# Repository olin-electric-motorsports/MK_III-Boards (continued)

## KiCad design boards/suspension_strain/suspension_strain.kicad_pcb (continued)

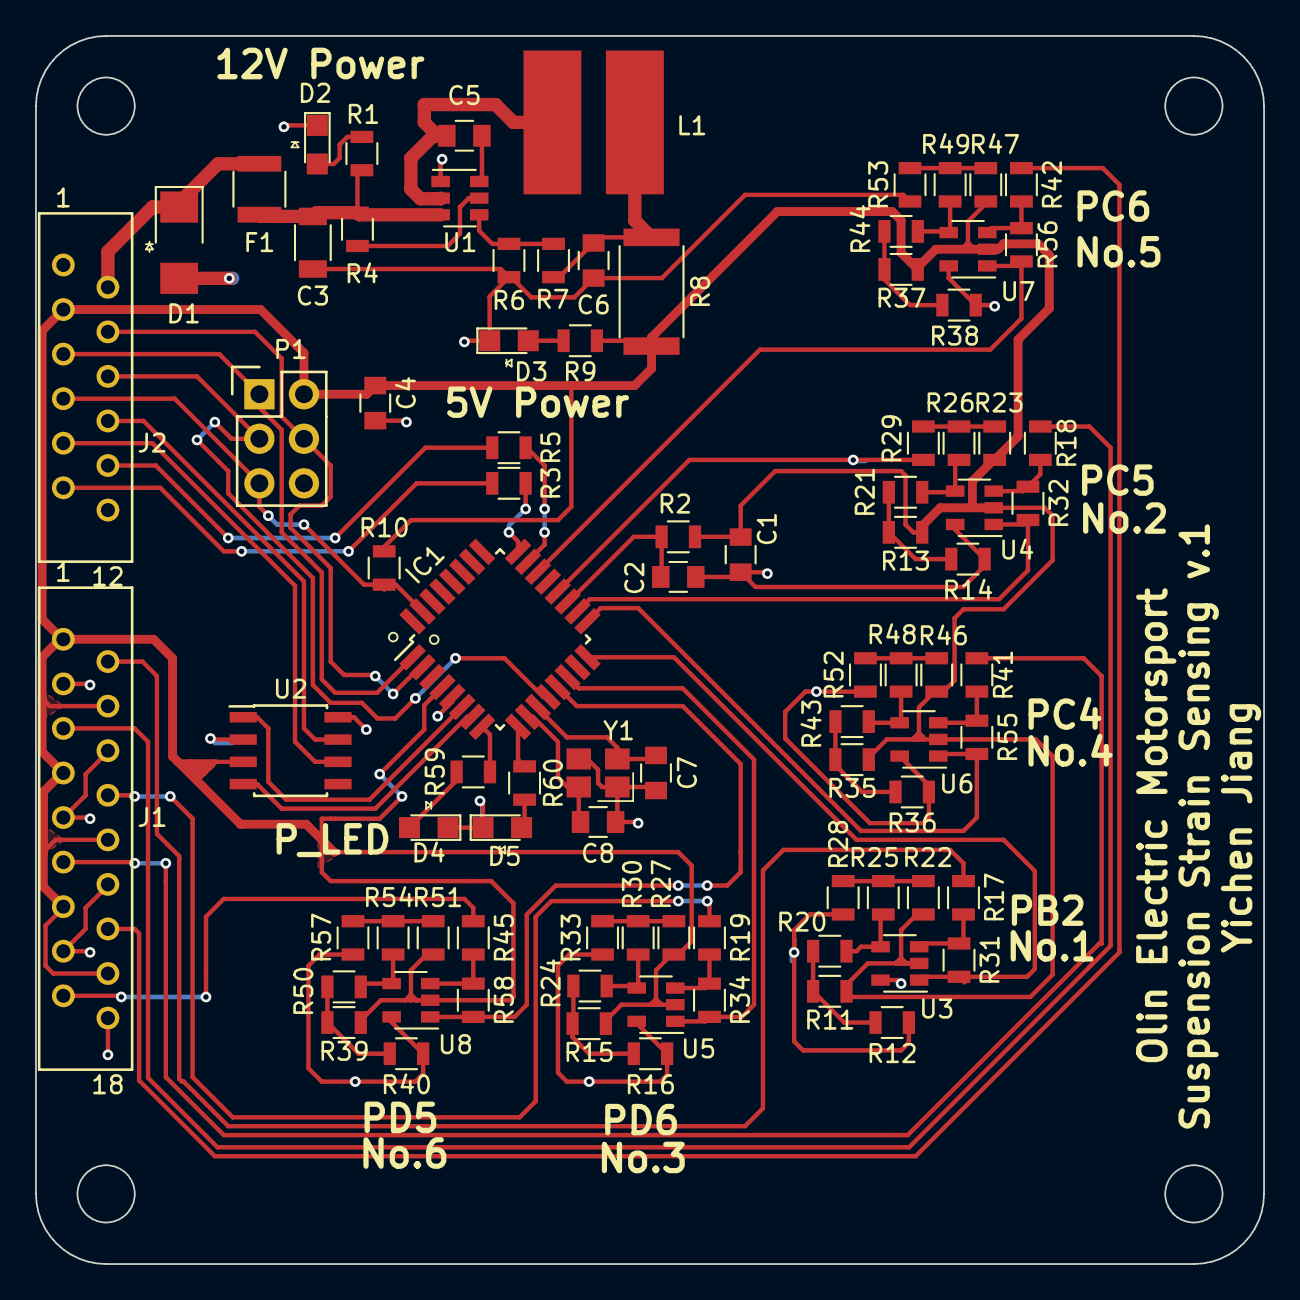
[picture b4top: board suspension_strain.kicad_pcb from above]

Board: 2 copper layers, 70.0 x 70.0 mm, 88 parts (0 on the bottom side), 66 nets.

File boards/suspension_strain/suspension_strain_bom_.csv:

Component,Description,Part,References,Value,Footprint,Quantity Per PCB,Datasheet,Package,MPN,MFN,PurchasingLink
1,Cap 50V 0.1uF 10% 0805,C_0.1uF,C1 C4 C5,C_0.1uF,C_0805_OEM,3,http://datasheets.avx.com/X7RDielectric.pdf,Value,478-3352-1-ND,Digi-Key,https://www.digikey.com/products/en?keywords=478-3352-1-ND
2,Cap 50V 100pF 5% 0805,C_100pF,C2,C_100pF,C_0805_OEM,1,https://content.kemet.com/datasheets/KEM_C1003_C0G_SMD.pdf,Value,399-1122-1-ND,Digi-Key,https://www.digikey.com/product-detail/en/kemet/C0805C101J5G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
3,Unpolarized capacitor,C_22uF,C3,C_22uF,C_1206_OEM,1,http://www.samsungsem.com/kr/support/product-search/mlcc/__i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,Value,1276-2725-1-ND,Digi-Key,https://www.digikey.com/products/en?keywords=1276-2725-1-ND
4,Cap 50V 30pF 5% 0805,C_30pF,C7 C8,C_30pF,C_0805_OEM,2,https://media.digikey.com/pdf/Data%20Sheets/Samsung%20PDFs/C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,Value,1276-1130-1-ND,Digi-Key,https://www.digikey.com/product-detail/en/samsung-electro-me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
5,CAP CER 47UF 6.3V X5R 0805,C_47uF,C6,C_47uF,C_0805_OEM,1,http://www.yuden.co.jp/productdata/catalog/en/mlcc_all_e.pdf,Value,587-4280-1-ND,Digi-Key,https://www.digikey.com/product-detail/en/taiyo-yuden/JMK212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
6,DIODE ZENER 18V 5W DO214AA,D_Zener_18V,D1,D_Zener_18V,DO-214AA,1,http://www.mccsemi.com/up_pdf/SMBJ5338B-SMBJ5388B(SMB).pdf,DO-214AA (SMB),SMBJ5355B-TPMSCT-ND,Digi-Key,https://www.digikey.com/products/en?keywords=SMBJ5355B-TPMSCT-ND
7,LED_0805,LED_0805,D2 D3 D4 D5,LED_0805,LED_0805_OEM,4,http://www.osram-os.com/Graphics/XPic9/00078860_0.pdf,Value,475-1410-1-ND,Digi-Key,https://www.digikey.com/products/en?keywords=475-1410-1-ND
8,PTC Fuse 16V 500mA,F_500mA_16V,F1,F_500mA_16V,Fuse_1210,1,https://belfuse.com/resources/CircuitProtection/datasheets/0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,Value,507-1786-1-ND,Digi-Key,https://www.digikey.com/product-detail/en/bel-fuse-inc/0ZCH0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
9,"TQFP32, 16k Flash, 1k SRAM, 512B EEPROM, CAN",ATMEGA16M1,IC1,ATMEGA16M1,TQFP-32_7x7mm_Pitch0.8mm,1,http://www.atmel.com/Images/Atmel-8209-8-bit%20AVR%20ATmega1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,Value,ATMEGA16M1-AU-ND,Digi-Key,https://www.digikey.com/product-detail/en/atmel/ATMEGA16M1-A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
10,connector micromatch female RA 12,micromatch_female_RA_12,J2,micromatch_female_RA_12,micromatch_female_ra_12,1,,Value,A99486CT-ND,Digi-Key,https://www.digikey.com/product-detail/en/te-connectivity-am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
11,connector micromatch female RA 18,micromatch_female_RA_18,J1,micromatch_female_RA_18,micromatch_female_ra_18,1,,Value,A99489CT-ND,Digi-Key,https://www.digikey.com/product-detail/en/te-connectivity-am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
12,Inductor 4.7uH 4.4A,L_4.7uH,L1,L_4.7uH,4.7uH_Inductor_OEM,1,https://product.tdk.com/info/en/documents/wdcatalog/withdraw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,Value,445-6583-1-ND,Digi-Key,https://www.digikey.com/product-detail/en/tdk-corporation/VL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
13,"Connector, double row, 02x03",CONN_02X03,P1,CONN_02X03,Pin_Header_Straight_2x03,1,http://portal.fciconnect.com/Comergent//fci/drawing/67996.pdf,Value,609-3234-ND,Digi-Key,https://www.digikey.com/product-detail/en/amphenol-fci/67997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
14,Res 0 2512 3W Jumper,R_0_Jumper,R8,R_0_Jumper,R_2512_OEM,1,http://www.te.com/commerce/DocumentDelivery/DDEController?Ac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,Value,A121322CT-ND,Digi-Key,https://www.digikey.com/products/en?keywords=A121322CT-ND
15,Res 100 1%,R_100,R2 R22 R23 R27 R28 R29 R33 R46 R47 R51 R52 R53 R57,R_100,R_0805_OEM,13,https://www.seielect.com/Catalog/SEI-rncp.pdf,Value,RNCP0805FTD100RCT-ND,Digi-Key,https://www.digikey.com/products/en?keywords=RNCP0805FTD100RCT-ND
16,Res 100k 1%,R_100k,R25 R26 R30 R31 R32 R34 R48 R49 R54 R55 R56 R58,R_100k,R_0805_OEM,12,http://www.yageo.com.tw/exep/pages/download/literatures/PYu-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,Value,311-100KCRCT-ND,Digi-Key,https://www.digikey.com/products/en?keywords=311-100KCRCT-ND
17,Res 10k 1%,R_10k,R4 R6 R10,R_10k,R_0805_OEM,3,http://www.bourns.com/data/global/pdfs/CRS.pdf,Value,CRS0805-FX-1002ELFCT-ND,Digi-Key,https://www.digikey.com/products/en?keywords=CRS0805-FX-1002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
18,Res 1k 1%,R_1k,R1 R17 R18 R19 R20 R21 R24 R41 R42 R43 R44 R45 R50,R_1k,R_0805_OEM,13,https://www.seielect.com/Catalog/SEI-rncp.pdf,Value,RNCP0805FTD1K00CT-ND,Digi-Key,https://www.digikey.com/products/en?keywords=RNCP0805FTD1K00CT-ND
19,Res 200 5%,R_200,R3 R5 R9 R59 R60,R_200,R_0805_OEM,5,https://www.seielect.com/Catalog/SEI-RMCF_RMCP.pdf,Value,RMCF0805JT200RCT-ND,Digi-Key,https://www.digikey.com/products/en?keywords=RMCF0805JT200RCT-ND
20,Resistor 500Ohm 0.1%,R_500,R11 R12 R13 R14 R15 R16 R35 R36 R37 R38 R39 R40,R_500,R_0805_OEM,12,http://www.vishay.com/docs/60057/pnm.pdf,Value,541-1905-2-ND,Digi Key,https://www.digikey.com/product-detail/en/vishay-dale/PNM040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
21,Res 55.1k 1%,R_55.1k,R7,R_55.1k,R_0805_OEM,1,http://www.yageo.com.tw/exep/pages/download/literatures/PYu-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,Value,311-51.1KCRCT-ND,Digi-Key,https://www.digikey.com/products/en?keywords=311-51.1KCRCT-ND
22,"High-Speed CAN Transceiver, 1Mbps, 5V supply, SPLIT pin, -40C to +125C, SOIC8 package",CAN_Transceiver,U2,CAN_Transceiver,SOIC-8_3.9x4.9mm_Pitch1.27mm_OEM,1,http://www.microchip.com/mymicrochip/filehandler.aspx?ddocna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,Value,MCP2561-E/SN-ND,Digi-Key,https://www.digikey.com/products/en?keywords=mcp2561-e%2Fsn
23,IC OPAMP GP 1MHZ RRO SOT23-5  1.8-6V,MCP6001RT,U3 U4 U5 U6 U7 U8,MCP6001RT,SOT-23-5_OEM,6,http://ww1.microchip.com/downloads/en/DeviceDoc/21733j.pdf,,MCP6001RT-I/OTCT-ND,Digi-Key,https://www.digikey.com/product-detail/en/microchip-technolo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
24,4.5V - 17V Input 1A Synchronous Buck Converter,TPS561201,U1,TPS561201,SOT-23-6_OEM,1,http://www.ti.com/lit/ds/symlink/tps561201.pdf,Value,TPS561201,Digi-Key,https://www.digikey.com/products/en?keywords=296-46928-1-ND
25,"Two pin crystal, two ground/package pins (pin2 and 3) small symbol",Crystal_SMD,Y1,Crystal_SMD,Crystal_SMD_FA238,1,https://support.epson.biz/td/api/doc_check.php?dl=brief_FA-2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,Value,SER3686CT-ND,Digi-Key,https://www.digikey.com/products/en?keywords=SER3686CT-ND





Component Groups:,25
Component Count:,88
Fitted Components:,88
Number of PCBs:,1
Total components:,88
Schematic Version:,
Schematic Date:,
BoM Date:,Tue 05 Dec 2017 08:39:58 PM EST
Schematic Source:,/home/yichen/Documents/Projects/Formula/MK_III-Boards/boards/suspension_strain/suspension_strain.sch
KiCad Version:,Eeschema 4.0.7-e2-6376~58~ubuntu16.04.1

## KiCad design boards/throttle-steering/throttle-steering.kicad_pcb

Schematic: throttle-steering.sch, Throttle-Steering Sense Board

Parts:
C1, C2, C5: C_0.1uF; C_0805_OEM; MPN 478-3352-1-ND
C3: C_100pF; C_0805_OEM; MPN 399-1122-1-ND
C4: C_22uF; C_1206_OEM; MPN 1276-2725-1-ND
C6, C8: C_30pF; C_0805_OEM; MPN 1276-1130-1-ND
C7: C_47uF; C_0805_OEM; MPN 587-4280-1-ND
D1, D2, D3, D4, D5, D6: LED_0805; LED_0805_OEM; MPN 475-1410-1-ND
D7: D_Zener_18V; DO-214AA; MPN SMBJ5355B-TPMSCT-ND
D8, D9: LED_0805; D_0805_OEM; MPN 475-1410-1-ND
F1: F_500mA_16V; Fuse_1210; MPN 507-1786-1-ND
IC1: ATMEGA16M1; TQFP-32_7x7mm_Pitch0.8mm; MPN ATMEGA16M1-AU-ND
J1: micromatch_female_RA_20; micromatch_female_ra_20; MPN A99490CT-ND
J2: micromatch_female_RA_4; micromatch_female_ra_4; MPN A99482CT-ND
L1: L_4.7uH; 4.7uH_Inductor_OEM; MPN 445-6583-1-ND
P1: CONN_02X03; Pin_Header_Straight_2x03; MPN 609-3234-ND
Q1, Q2, Q3: SSM3K333R; SOT-23F; MPN SSM3K333RLFCT-ND
R1, R2, R3, R24, R25, R28: R_200; R_0805_OEM; MPN RMCF0805JT200RCT-ND
R4, R13: R_1M; R_0805_OEM; MPN RMCF0805JT1M00CT-ND
R5, R7, R10, R15, R16, R20: R_1k; R_0805_OEM; MPN RNCP0805FTD1K00CT-ND
R6, R11, R17: R_100k; R_0805_OEM; MPN 311-100KCRCT-ND
R8, R14: R_2.2k; R_0805_OEM; MPN RMCF0805FT2K20CT-ND
R9, R12, R18, R21, R22, R27: R_10k; R_0805_OEM; MPN CRS0805-FX-1002ELFCT-ND
R19: R_100; R_0805_OEM; MPN RNCP0805FTD100RCT-ND
R23: R_55.1k; R_0805_OEM; MPN 311-51.1KCRCT-ND
R26: R_0_Jumper; R_2512_OEM; MPN A121322CT-ND
U1, U3: MCP6001RT; SOT-23-5_OEM; MPN MCP6001RT-I/OTCT-ND
U2: CAN_Transceiver; SOIC-8_3.9x4.9mm_Pitch1.27mm_OEM; MPN MCP2561-E/SN-ND
U4: TPS561201; SOT-23-6_OEM; MPN TPS561201
Y1: Crystal_SMD; Crystal_SMD_FA238; MPN SER3686CT-ND

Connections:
+12V: D7.1 (K), F1.1, J2.2
/CANH: J2.8, U2.7 (CANH)
/CANL: J2.9, U2.6 (CANL)
/LED1: J2.10, R24.1
/LED2: J2.11, R25.1
/MISO: IC1.1 ((PCINT18/PSCIN2/OC1A/MISO_A)PD2), J2.5, P1.1
/MOSI: IC1.2 ((PCINT19/TXD/TXLIN/OC0A/~SS~/MOSI_A)PD3), J2.4, P1.4
/PLED1: D1.2 (A), IC1.22 ((PCINT14/ADC10/ACMP1)PC6)
/PLED2: D2.2 (A), IC1.23 ((PCINT3/AMP0-)PB3)
/PLED3: D3.2 (A), IC1.24 ((PCINT4/AMP0+)PB4)
/RESET: IC1.31 ((PCINT24/OCD/~RESET~)PE0), J2.7, P1.5, R27.2
/RTD: J1.4; also elsewhere on the board
/RXCAN: IC1.7 ((PCINT11/T1/ICP1B/RXCAN)PC3), U2.4 (RXD)
/SCK: IC1.12 ((PCINT20/ADC1/RXD/RXLIN/ICP1A/SCK_A)PD4), J2.6, P1.3
/SS_BOTS: J1.1, Q3.1 (G), R16.1, R17.1
/SS_BOTS_Out: IC1.28 ((PCINT7/ADC4/SCK/PSCOUT0B)PB7), Q3.3 (D), R18.2
/SS_Cockpit_EStop: J1.2, Q2.1 (G), R10.1, R11.1
/SS_EStop_Out: IC1.27 ((PCINT6/ADC7/PSCOUT1B)PB6), Q2.3 (D), R12.2
/SS_IS_Out: IC1.26 ((PCINT5/ADC6/INT2/ACMPN1/AMP2-)PB5), Q1.3 (D), R9.2
/SS_Inertia_Switch: J1.3, Q1.1 (G), R5.1, R6.1
/Steering_Sense: IC1.13 ((PCINT21/ADC2/ACMP2)PD5), J2.19
/TXCAN: IC1.6 ((PCINT10/T0/TXCAN)PC2), U2.1 (TXD)
/Throttle1OutL: IC1.17 ((PCINT12/ADC8/ACMPN3/AMP1-)PC4), R14.1, U3.1
/Throttle2OutR: IC1.18 ((PCINT13/ADC9/ACMP3/AMP1+)PC5), R7.1, U1.1
/Throttle_Left_Sense: J2.13, R13.2, U3.3 (+)
/Throttle_Right_Sense: J2.16, R4.2, U1.3 (+)
GND: C1.2, C2.2, C3.2, C4.2, C6.2, C7.2, C8.2, D4.1 (K), D5.1 (K), D6.1 (K), D7.2 (A), D8.1 (K), D9.1 (K), IC1.5 (GND), IC1.20 (AGND), J2.1, J2.14, J2.17, J2.20, P1.6, Q1.2 (S), Q2.2 (S), Q3.2 (S), R1.2, R2.2, R3.2, R6.2, R8.2, R11.2, R15.2, R17.2, R22.2, U1.5 (V-), U2.2 (VSS), U2.8 (STBY), U3.5 (V-), U4.1 (GND), Y1.2, Y1.4; also elsewhere on the board
unnamed: C3.1, IC1.19 (AVCC), R19.2
unnamed: C4.1, F1.2, R20.1, R21.1, U4.3 (VIN)
unnamed: C5.1, U4.6 (VBST)
unnamed: C5.2, L1.1, U4.2 (SW)
unnamed: C6.1, IC1.11 ((PCINT26/ADC0/XTAL2)PE2), Y1.1
unnamed: C8.1, IC1.10 ((PCINT25/OC0B/XTAL1)PE1), Y1.3
unnamed 33: C7.1, L1.2, R23.2, R26.2; also elsewhere on the board
unnamed: D1.1 (K), R1.1
unnamed: D2.1 (K), R2.1
unnamed: D3.1 (K), R3.1
unnamed: D4.2 (A), R5.2
unnamed: D5.2 (A), R10.2
unnamed: D6.2 (A), R16.2
unnamed: D8.2 (A), R20.2
unnamed: D9.2 (A), R28.2
unnamed: IC1.8 ((PCINT0/MISO/PSCOUT2A)PB0), R24.2
unnamed: IC1.9 ((PCINT1/MOSI/PSCOUT2B)PB1), R25.2
unnamed: R7.2, R8.1, U1.4 (-)
unnamed: R14.2, R15.1, U3.4 (-)
unnamed: R21.2, U4.5 (EN)
unnamed: R22.1, R23.1, U4.4 (VFB)
RTD_LD: IC1.25 ((PCINT15/D2A/AMP2+)PC7); also elsewhere on the board
VCC: C1.1, C2.1, IC1.4 (VCC), J2.3, J2.12, J2.15, J2.18, P1.2, R4.1, R9.1, R12.1, R13.1, R18.1, R19.1, R26.1, R27.1, R28.1, U1.2 (V+), U2.3 (VDD), U3.2 (V+); also elsewhere on the board

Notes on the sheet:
Shutdown Sense Circuits
Throttle Sensor Circuits
Programming LED's
Buck Converter
RTD-Low Drive

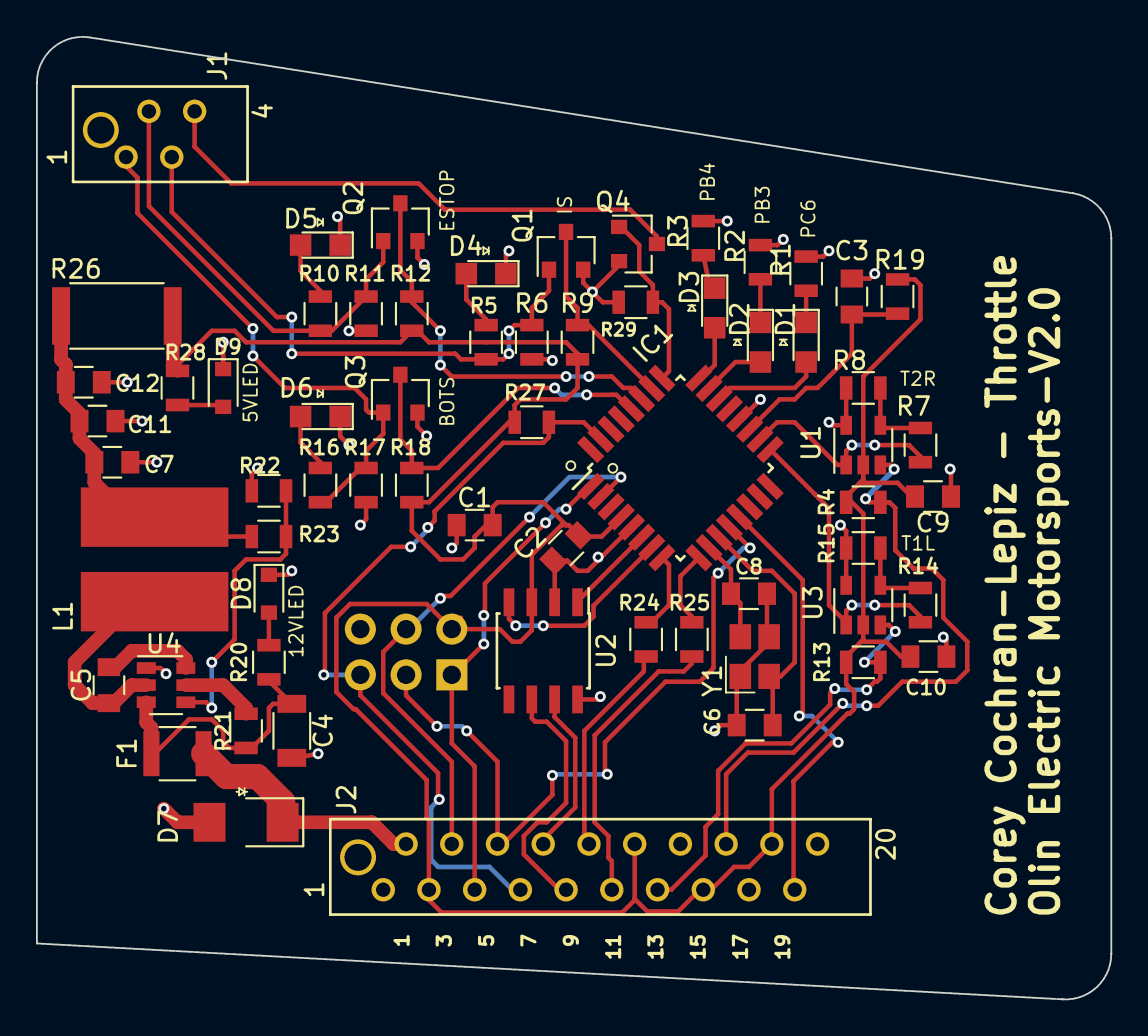
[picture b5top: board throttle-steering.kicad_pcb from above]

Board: 2 copper layers, 59.7 x 53.5 mm, 65 parts (1 on the bottom side), 50 nets.

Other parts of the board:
C9, C10: C_0.1uF; C_0805_OEM
C11: 1uF; C_0805_OEM
C12: 0.1uF; C_0805_OEM
Q4: SSM3K333R; SOT-23F
R29: R_100k; R_0805_OEM

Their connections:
/RTD: Q4.3; also elsewhere on the board
GND: C9.1, C10.1, C11.2, C12.2, Q4.2, R29.2; also elsewhere on the board
unnamed 33: C11.1, C12.1; also elsewhere on the board
RTD_LD: Q4.1, R29.1; also elsewhere on the board
VCC: C9.2, C10.2; also elsewhere on the board

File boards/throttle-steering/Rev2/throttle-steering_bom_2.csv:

Component,Description,Part,References,Value,Footprint,Quantity Per PCB,Datasheet,Package,MPN,MFN,PurchasingLink,Purchase_Link
1,Cap 50V 0.1uF 10% 0805,C_0.1uF,C12,0.1uF,C_0805_OEM,1,http://datasheets.avx.com/X7RDielectric.pdf,Value,478-3352-1-ND,Digi-Key,https://www.digikey.com/products/en?keywords=478-3352-1-ND,
2,CAP CER 1UF 25V X7R 0805,C_1uF,C11,1uF,C_0805_OEM,1,http://datasheets.avx.com/X7RDielectric.pdf,Value,478-10487-1-ND,Digi-Key,https://www.digikey.com/product-detail/en/avx-corporation/08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,
3,CAP CER 47UF 6.3V X5R 0805,C_47uF,C7,47uF,C_0805_OEM,1,http://www.yuden.co.jp/productdata/catalog/en/mlcc_all_e.pdf,Value,587-4280-1-ND,Digi-Key,https://www.digikey.com/product-detail/en/taiyo-yuden/JMK212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,
4,Cap 50V 0.1uF 10% 0805,C_0.1uF,C1 C2 C5 C9 C10,C_0.1uF,C_0805_OEM,5,http://datasheets.avx.com/X7RDielectric.pdf,Value,478-3352-1-ND,Digi-Key,https://www.digikey.com/products/en?keywords=478-3352-1-ND,
5,Cap 50V 100pF 5% 0805,C_100pF,C3,C_100pF,C_0805_OEM,1,https://content.kemet.com/datasheets/KEM_C1003_C0G_SMD.pdf,Value,399-1122-1-ND,Digi-Key,https://www.digikey.com/product-detail/en/kemet/C0805C101J5G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,
6,Unpolarized capacitor,C_22uF,C4,C_22uF,C_1206_OEM,1,http://www.samsungsem.com/kr/support/product-search/mlcc/__i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,Value,1276-2725-1-ND,Digi-Key,https://www.digikey.com/products/en?keywords=1276-2725-1-ND,
7,Cap 50V 30pF 5% 0805,C_30pF,C6 C8,C_30pF,C_0805_OEM,2,https://media.digikey.com/pdf/Data%20Sheets/Samsung%20PDFs/C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,Value,1276-1130-1-ND,Digi-Key,https://www.digikey.com/product-detail/en/samsung-electro-me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,
8,DIODE ZENER 18V 5W DO214AA,D_Zener_18V,D7,D_Zener_18V,DO-214AA,1,http://www.mccsemi.com/up_pdf/SMBJ5338B-SMBJ5388B(SMB).pdf,DO-214AA (SMB),SMBJ5355B-TPMSCT-ND,Digi-Key,https://www.digikey.com/products/en?keywords=SMBJ5355B-TPMSCT-ND,
9,LED_0805,LED_0805,D1 D2 D3 D4 D5 D6,LED_0805,LED_0805_OEM,6,http://www.osram-os.com/Graphics/XPic9/00078860_0.pdf,Value,475-1410-1-ND,Digi-Key,https://www.digikey.com/products/en?keywords=475-1410-1-ND,
10,LED_0805,LED_0805,D8 D9,LED_0805,D_0805_OEM,2,http://www.osram-os.com/Graphics/XPic9/00078860_0.pdf,Value,475-1410-1-ND,Digi-Key,https://www.digikey.com/products/en?keywords=475-1410-1-ND,
11,PTC Fuse 16V 500mA,F_500mA_16V,F1,F_500mA_16V,Fuse_1210,1,https://belfuse.com/resources/CircuitProtection/datasheets/0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,Value,507-1786-1-ND,Digi-Key,https://www.digikey.com/product-detail/en/bel-fuse-inc/0ZCH0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,
12,"TQFP32, 16k Flash, 1k SRAM, 512B EEPROM, CAN",ATMEGA16M1,IC1,ATMEGA16M1,TQFP-32_7x7mm_Pitch0.8mm,1,http://www.atmel.com/Images/Atmel-8209-8-bit%20AVR%20ATmega1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,Value,ATMEGA16M1-AU-ND,Digi-Key,https://www.digikey.com/product-detail/en/atmel/ATMEGA16M1-A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,
13,CONN FMALE-ON-BRD 20POS VERT T/H,micromatch_female_TOP_ENTRY_locking_20,J2,micromatch_female_TOP_ENTRY_locking_20,micromatch_female_vert_20,1,,Value,A99499CT-ND,Digi-Key,https://www.digikey.com/product-detail/en/te-connectivity-am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,
14,CONN FMALE-ON-BRD 4POS VERT T/H,micromatch_female_TOP_ENTRY_locking_4,J1,micromatch_female_TOP_ENTRY_locking_4,micromatch_female_vert_4,1,http://www.te.com/commerce/DocumentDelivery/DDEController?Ac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,Value,338068-4,Digi-Key,https://www.digikey.com/product-detail/en/te-connectivity-am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,
15,Inductor 4.7uH 4.4A,L_4.7uH,L1,L_4.7uH,4.7uH_Inductor_OEM,1,https://product.tdk.com/info/en/documents/wdcatalog/withdraw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,Value,445-6583-1-ND,Digi-Key,https://www.digikey.com/product-detail/en/tdk-corporation/VL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,
16,"Connector, double row, 02x03",CONN_02X03,P1,CONN_02X03,Pin_Header_Straight_2x03,1,http://portal.fciconnect.com/Comergent//fci/drawing/67996.pdf,Value,609-3234-ND,Digi-Key,https://www.digikey.com/product-detail/en/amphenol-fci/67997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,
17,"60V Vds, 0.115A Id, N-channel MOSFET, SOT-23",SSM3K333R,Q1 Q2 Q3 Q4,SSM3K333R,SOT-23F,4,file:///home/sherrieshen/Downloads/SSM3K333R_datasheet_en_20140301.pdf,SOT-23-3 Flat Leads,SSM3K333RLFCT-ND,Digi-Key,,https://www.digikey.com/product-detail/en/toshiba-semiconduc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
18,Res 0 2512 3W Jumper,R_0_Jumper,R26,R_0_Jumper,R_2512_OEM,1,http://www.te.com/commerce/DocumentDelivery/DDEController?Ac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,Value,A121322CT-ND,Digi-Key,https://www.digikey.com/products/en?keywords=A121322CT-ND,
19,Res 100 1%,R_100,R19,R_100,R_0805_OEM,1,https://www.seielect.com/Catalog/SEI-rncp.pdf,Value,RNCP0805FTD100RCT-ND,Digi-Key,https://www.digikey.com/products/en?keywords=RNCP0805FTD100RCT-ND,
20,Res 100k 1%,R_100k,R6 R11 R17 R29,R_100k,R_0805_OEM,4,http://www.yageo.com.tw/exep/pages/download/literatures/PYu-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,Value,311-100KCRCT-ND,Digi-Key,https://www.digikey.com/products/en?keywords=311-100KCRCT-ND,
21,Res 10k 1%,R_10k,R9 R12 R18 R21 R22 R27,R_10k,R_0805_OEM,6,http://www.bourns.com/data/global/pdfs/CRS.pdf,Value,CRS0805-FX-1002ELFCT-ND,Digi-Key,https://www.digikey.com/products/en?keywords=CRS0805-FX-1002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,
22,RES SMD 1M OHM 5% 1/8W 0805,R_1M,R4 R13,R_1M,R_0805_OEM,2,https://www.seielect.com/Catalog/SEI-rncp.pdf,Value,RMCF0805JT1M00CT-ND,Digi-Key,https://www.digikey.com/product-detail/en/stackpole-electron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,
23,Res 1k 1%,R_1k,R5 R7 R10 R16 R20,R_1k,R_0805_OEM,5,https://www.seielect.com/Catalog/SEI-rncp.pdf,Value,RNCP0805FTD1K00CT-ND,Digi-Key,https://www.digikey.com/products/en?keywords=RNCP0805FTD1K00CT-ND,
24,RES SMD 2.2K OHM 1% 1/8W 0805,R_2.2k,R8 R14 R15,R_2.2k,R_0805_OEM,3,https://www.seielect.com/Catalog/SEI-RMCF_RMCP.pdf,Value,RMCF0805FT2K20CT-ND,Digi-Key,https://www.digikey.com/product-detail/en/stackpole-electron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,
25,Res 200 5%,R_200,R1 R2 R3 R24 R25 R28,R_200,R_0805_OEM,6,https://www.seielect.com/Catalog/SEI-RMCF_RMCP.pdf,Value,RMCF0805JT200RCT-ND,Digi-Key,https://www.digikey.com/products/en?keywords=RMCF0805JT200RCT-ND,
26,Res 55.1k 1%,R_55.1k,R23,R_55.1k,R_0805_OEM,1,http://www.yageo.com.tw/exep/pages/download/literatures/PYu-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,Value,311-51.1KCRCT-ND,Digi-Key,https://www.digikey.com/products/en?keywords=311-51.1KCRCT-ND,
27,"High-Speed CAN Transceiver, 1Mbps, 5V supply, SPLIT pin, -40C to +125C, SOIC8 package",CAN_Transceiver,U2,CAN_Transceiver,SOIC-8_3.9x4.9mm_Pitch1.27mm_OEM,1,http://www.microchip.com/mymicrochip/filehandler.aspx?ddocna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,Value,MCP2561-E/SN-ND,Digi-Key,https://www.digikey.com/products/en?keywords=mcp2561-e%2Fsn,
28,IC OPAMP GP 1MHZ RRO SOT23-5  1.8-6V,MCP6001RT,U1 U3,MCP6001RT,SOT-23-5_OEM,2,http://ww1.microchip.com/downloads/en/DeviceDoc/21733j.pdf,Value,MCP6001RT-I/OTCT-ND,Digi-Key,https://www.digikey.com/product-detail/en/microchip-technolo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,
29,4.5V - 17V Input 1A Synchronous Buck Converter,TPS561201,U4,TPS561201,SOT-23-6_OEM,1,http://www.ti.com/lit/ds/symlink/tps561201.pdf,Value,TPS561201,Digi-Key,https://www.digikey.com/products/en?keywords=296-46928-1-ND,
30,"Two pin crystal, two ground/package pins (pin2 and 3) small symbol",Crystal_SMD,Y1,Crystal_SMD,Crystal_SMD_FA238,1,https://support.epson.biz/td/api/doc_check.php?dl=brief_FA-2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,Value,SER3686CT-ND,Digi-Key,https://www.digikey.com/products/en?keywords=SER3686CT-ND,





Component Groups:,30
Component Count:,65
Fitted Components:,65
Number of PCBs:,1
Total components:,65
Schematic Version:,2
Schematic Date:,2/2/2018
BoM Date:,Sun 11 Feb 2018 10:46:42 AM EST
Schematic Source:,/home/corey/Desktop/Formula/MK_III-Boards/boards/throttle-steering/throttle-steering.sch
KiCad Version:,Eeschema 4.0.7-e2-6376~58~ubuntu16.04.1

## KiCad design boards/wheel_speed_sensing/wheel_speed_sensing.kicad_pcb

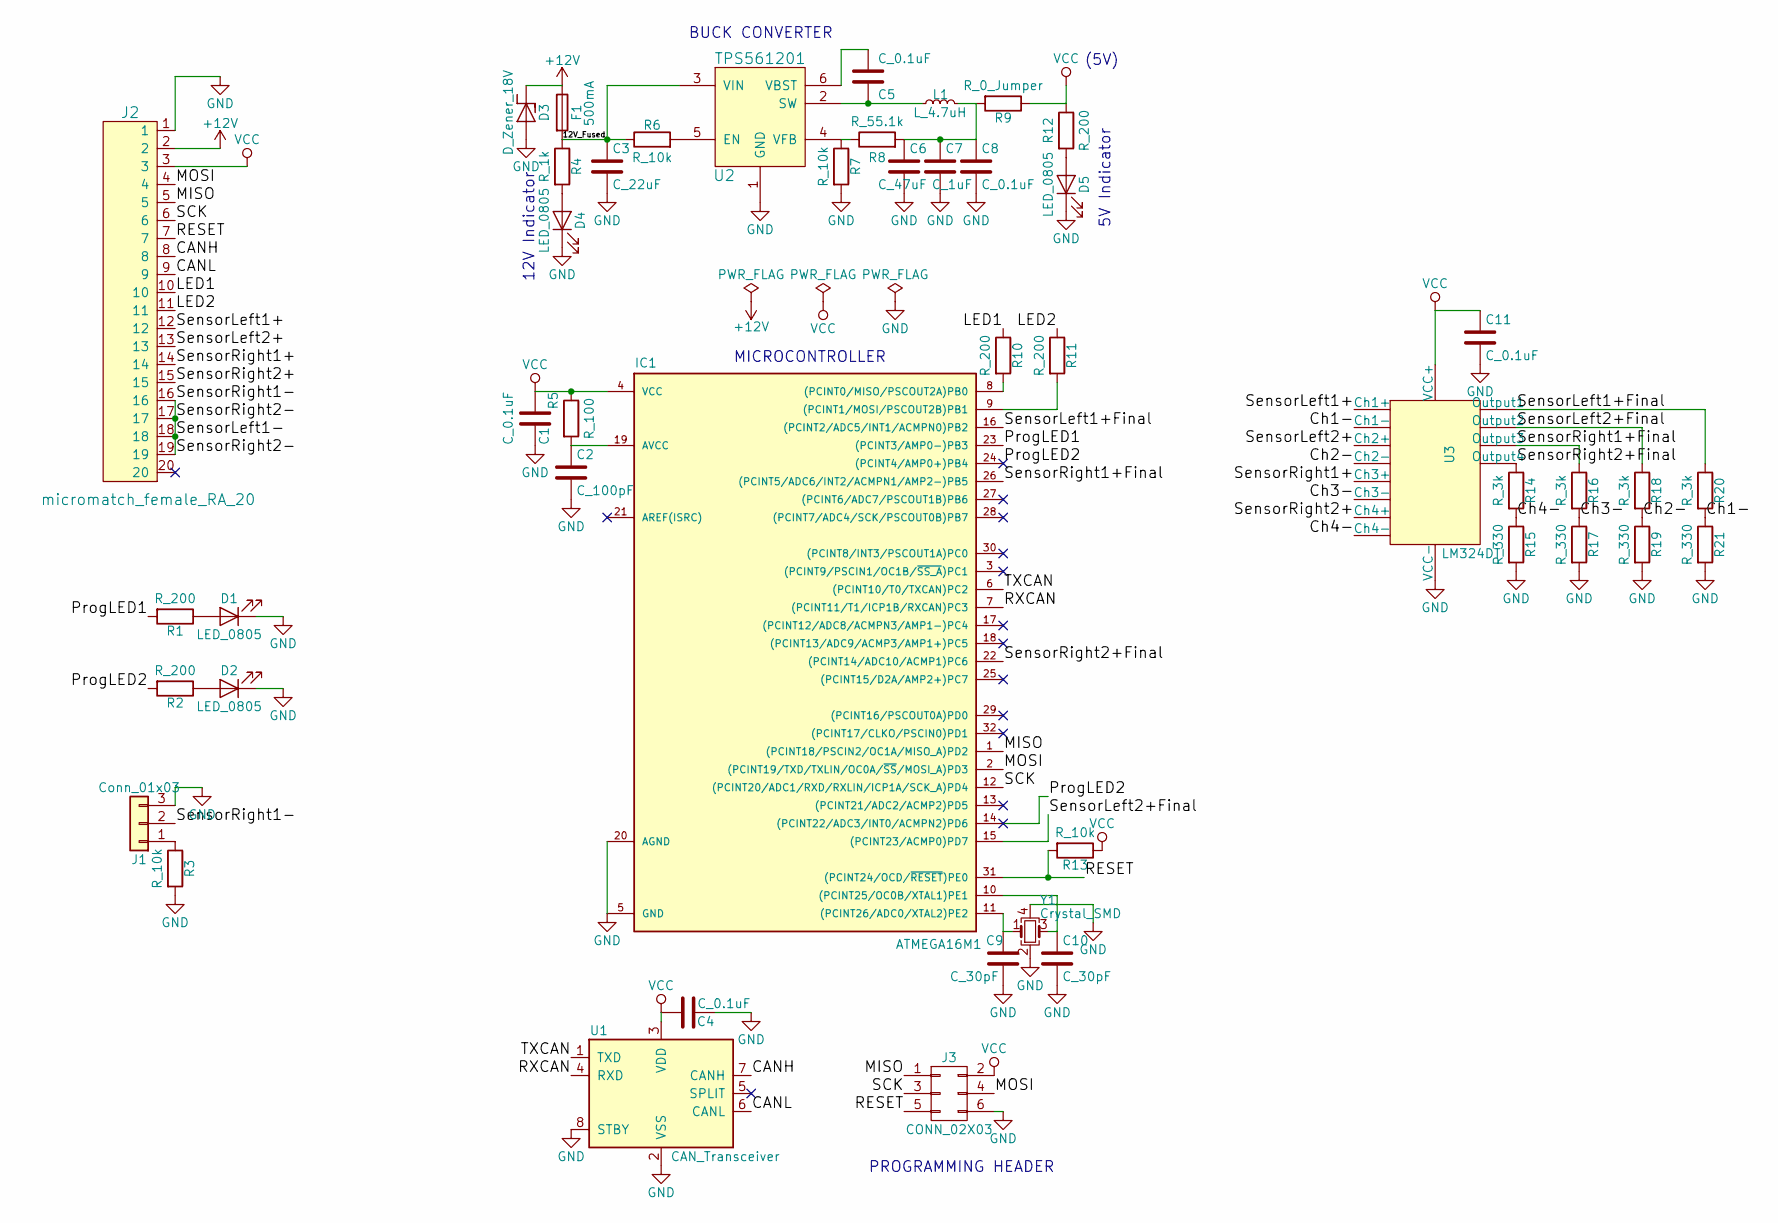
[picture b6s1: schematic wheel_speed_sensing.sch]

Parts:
C1, C4, C5: C_0.1uF; C_0805; MPN 478-3352-1-ND
C2: C_100pF; C_0805; MPN 399-1122-1-ND
C3: C_22uF; C_1206; MPN 1276-2725-1-ND
C6: C_47uF; C_0805; MPN 587-4280-1-ND
C7: C_1uF; C_0805_OEM; MPN 478-10487-1-ND
C8, C11: C_0.1uF; C_0805_OEM; MPN 478-3352-1-ND
C9, C10: C_30pF; C_0805; MPN 1276-1130-1-ND
D1, D2: LED_0805; LED_0805_OEM; MPN 475-1410-1-ND
D3: D_Zener_18V; DO-214AA; MPN SMBJ5355B-TPMSCT-ND
D4, D5: LED_0805; MPN 475-1410-1-ND
F1: 500mA; Fuse_1210; MPN 507-1786-1-ND
IC1: ATMEGA16M1; TQFP-32_7x7mm_Pitch0.8mm; MPN ATMEGA16M1-AU-ND
J1: Conn_01x03; Pin_Header_Straight_1x03_Pitch2.54mm
J2: micromatch_female_RA_20; micromatch_female_ra_20; MPN A99490CT-ND
J3: CONN_02X03; Pin_Header_Straight_2x03; MPN 609-3234-ND
L1: L_4.7uH; 4.7uH_Inductor_OEM; MPN 445-6583-1-ND
R1, R2, R10, R11: R_200; R_0805_OEM; MPN RMCF0805JT200RCT-ND
R3: R_10k; R_0805_OEM; MPN CRS0805-FX-1002ELFCT-ND
R4: R_1k; R_0805; MPN RNCP0805FTD1K00CT-ND
R5: R_100; R_0805; MPN RNCP0805FTD100RCT-ND
R6, R7, R13: R_10k; R_0805; MPN CRS0805-FX-1002ELFCT-ND
R8: R_55.1k; R_0805; MPN 311-51.1KCRCT-ND
R9: R_0_Jumper; R_2512; MPN A121322CT-ND
R12: R_200; R_0805; MPN RMCF0805JT200RCT-ND
R14, R16, R18, R20: R_3k; R_0805_OEM; MPN RMCF0805FT3K00CT-ND
R15, R17, R19, R21: R_330; R_0805_OEM; MPN RMCF0805FT330RCT-ND
U1: CAN_Transceiver; SOIC-8_3.9x4.9mm_Pitch1.27mm; MPN MCP2561-E/SN-ND
U2: TPS561201; SOT-23-6; MPN TPS561201
U3: LM324DT; SOIC-14_3.9x8.7mm_Pitch1.27mm; MPN 497-1580-1-ND
Y1: Crystal_SMD; Crystal_SMD_FA238; MPN SER3686CT-ND

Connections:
+12V: D3.1 (K), F1.1, J2.2
/12V_Fused: C3.1, F1.2, R4.1, R6.1, U2.3 (VIN)
/CANH: J2.8, U1.7 (CANH)
/CANL: J2.9, U1.6 (CANL)
/Ch1-: R20.2, R21.1, U3.2 (Ch1-)
/Ch2-: R18.2, R19.1, U3.6 (Ch2-)
/Ch3-: R16.2, R17.1, U3.9 (Ch3-)
/Ch4-: R14.2, R15.1, U3.13 (Ch4-)
/LED1: J2.10, R10.1
/LED2: J2.11, R11.1
/MISO: IC1.1 ((PCINT18/PSCIN2/OC1A/MISO_A)PD2), J2.5, J3.1
/MOSI: IC1.2 ((PCINT19/TXD/TXLIN/OC0A/~SS~/MOSI_A)PD3), J2.4, J3.4
/ProgLED1: IC1.23 ((PCINT3/AMP0-)PB3), R1.2
/RESET: IC1.31 ((PCINT24/OCD/~RESET~)PE0), J2.7, J3.5, R13.2
/RXCAN: IC1.7 ((PCINT11/T1/ICP1B/RXCAN)PC3), U1.4 (RXD)
/SCK: IC1.12 ((PCINT20/ADC1/RXD/RXLIN/ICP1A/SCK_A)PD4), J2.6, J3.3
/SensorLeft1+: J2.12, U3.3 (Ch1+)
/SensorLeft1+Final: IC1.16 ((PCINT2/ADC5/INT1/ACMPN0)PB2), R20.1, U3.1 (Output1)
/SensorLeft1-: J1.2, J2.16, J2.17, J2.18, J2.19
/SensorLeft2+: J2.13, U3.5 (Ch2+)
/SensorLeft2+Final: IC1.15 ((PCINT23/ACMP0)PD7), R18.1, U3.7 (Output2)
/SensorRight1+: J2.14, U3.10 (Ch3+)
/SensorRight1+Final: IC1.26 ((PCINT5/ADC6/INT2/ACMPN1/AMP2-)PB5), R16.1, U3.8 (Output3)
/SensorRight2+: J2.15, U3.12 (Ch4+)
/SensorRight2+Final: IC1.22 ((PCINT14/ADC10/ACMP1)PC6), R14.1, U3.14 (Output4)
/TXCAN: IC1.6 ((PCINT10/T0/TXCAN)PC2), U1.1 (TXD)
GND: C1.2, C2.2, C3.2, C4.2, C6.2, C7.2, C8.2, C9.2, C10.2, C11.2, D1.1 (K), D2.1 (K), D3.2 (A), D4.1 (K), D5.1 (K), IC1.5 (GND), IC1.20 (AGND), J1.3, J2.1, J3.6, R3.2, R7.2, R15.2, R17.2, R19.2, R21.2, U1.2 (VSS), U1.8 (STBY), U2.1 (GND), U3.11 (VCC-), Y1.2, Y1.4
unnamed: C2.1, IC1.19 (AVCC), R5.2
unnamed: C5.1, U2.6 (VBST)
unnamed: C5.2, L1.1, U2.2 (SW)
unnamed: C6.1, C7.1, C8.1, L1.2, R8.2, R9.2
unnamed: C9.1, IC1.11 ((PCINT26/ADC0/XTAL2)PE2), Y1.1
unnamed: C10.1, IC1.10 ((PCINT25/OC0B/XTAL1)PE1), Y1.3
unnamed: D1.2 (A), R1.1
unnamed: D2.2 (A), R2.1
unnamed: D4.2 (A), R4.2
unnamed: D5.2 (A), R12.2
unnamed: IC1.8 ((PCINT0/MISO/PSCOUT2A)PB0), R10.2
unnamed: IC1.9 ((PCINT1/MOSI/PSCOUT2B)PB1), R11.2
unnamed: J1.1, R3.1
unnamed: R6.2, U2.5 (EN)
unnamed: R7.1, R8.1, U2.4 (VFB)
VCC: C1.1, C4.1, C11.1, IC1.4 (VCC), J2.3, J3.2, R5.1, R9.1, R12.1, R13.1, U1.3 (VDD), U3.4 (VCC+)

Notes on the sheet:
BUCK CONVERTER
12V Indicator
5V Indicator
(5V)
MICROCONTROLLER
PROGRAMMING HEADER

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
